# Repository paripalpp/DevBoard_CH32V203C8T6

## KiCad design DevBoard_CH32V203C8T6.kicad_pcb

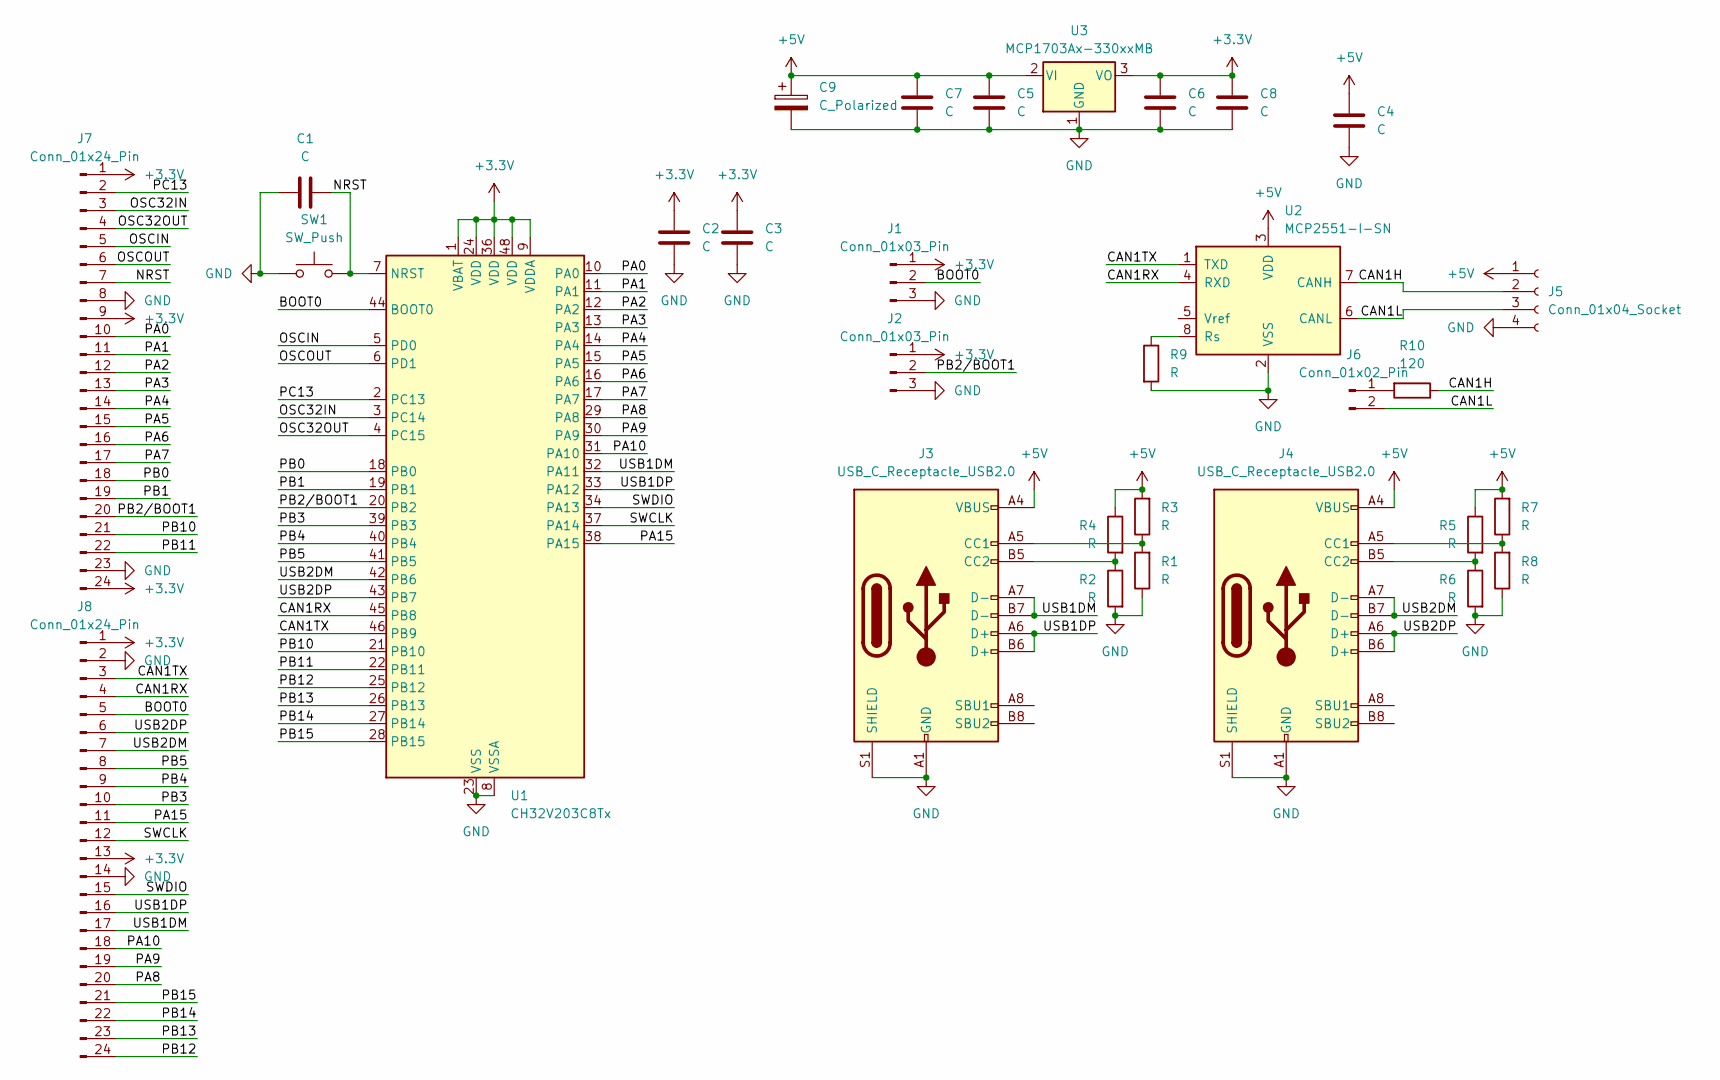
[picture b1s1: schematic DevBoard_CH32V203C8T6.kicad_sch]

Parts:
C1, C2, C3, C4, C5, C6: C; C_0603_1608Metric
C7, C8: C; C_0805_2012Metric
C9: C_Polarized; CP_Elec_6.3x7.7
J1, J2: Conn_01x03_Pin; PinHeader_1x03_P2.54mm_Vertical
J3, J4: USB_C_Receptacle_USB2.0; USB_C_Receptacle_G-Switch_GT-USB-7010ASV
J5: Conn_01x04_Socket; JST_XA_S04B-XASK-1_1x04_P2.50mm_Horizontal
J6: Conn_01x02_Pin; PinHeader_1x02_P2.54mm_Vertical
J7, J8: Conn_01x24_Pin; PinHeader_2x12_P2.54mm_Vertical
R1, R2, R3, R4, R5, R6, R7, R8, R9: R; R_0603_1608Metric
R10: 120; R_0603_1608Metric
SW1: SW_Push; TVAF06-A020B-R
U1: CH32V203C8Tx; LQFP-48_7x7mm_P0.5mm
U2: MCP2551-I-SN; SOIC-8_3.9x4.9mm_P1.27mm
U3: MCP1703Ax-330xxMB; SOT-89-3

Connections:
+3.3V: C2.1, C3.1, C6.1, C8.1, J1.1, J2.1, J7.1, J7.9, J7.24, J8.1, J8.13, U1.1 (VBAT), U1.9 (VDDA), U1.24 (VDD), U1.36 (VDD), U1.48 (VDD), U3.3 (VO)
+5V: C4.1, C5.1, C7.1, C9.1, J3.A4 (VBUS), J3.A9 (VBUS), J3.B4 (VBUS), J3.B9 (VBUS), J4.A4 (VBUS), J4.A9 (VBUS), J4.B4 (VBUS), J4.B9 (VBUS), J5.1, R3.2, R4.1, R5.1, R7.2, U2.3 (VDD), U3.2 (VI)
/BOOT0: J1.2, J8.5, U1.44 (BOOT0)
/CAN1H: J5.2, R10.1, U2.7 (CANH)
/CAN1L: J5.3, J6.2, U2.6 (CANL)
/CAN1RX: J8.4, U1.45 (PB8), U2.4 (RXD)
/CAN1TX: J8.3, U1.46 (PB9), U2.1 (TXD)
/NRST: C1.2, J7.7, SW1.2, U1.7 (NRST)
/OSC32IN: J7.3, U1.3 (PC14)
/OSC32OUT: J7.4, U1.4 (PC15)
/OSCIN: J7.5, U1.5 (PD0)
/OSCOUT: J7.6, U1.6 (PD1)
/PA0: J7.10, U1.10 (PA0)
/PA1: J7.11, U1.11 (PA1)
/PA2: J7.12, U1.12 (PA2)
/PA3: J7.13, U1.13 (PA3)
/PA4: J7.14, U1.14 (PA4)
/PA5: J7.15, U1.15 (PA5)
/PA6: J7.16, U1.16 (PA6)
/PA7: J7.17, U1.17 (PA7)
/PA8: J8.20, U1.29 (PA8)
/PA9: J8.19, U1.30 (PA9)
/PA10: J8.18, U1.31 (PA10)
/PA15: J8.11, U1.38 (PA15)
/PB0: J7.18, U1.18 (PB0)
/PB1: J7.19, U1.19 (PB1)
/PB2/BOOT1: J2.2, J7.20, U1.20 (PB2)
/PB3: J8.10, U1.39 (PB3)
/PB4: J8.9, U1.40 (PB4)
/PB5: J8.8, U1.41 (PB5)
/PB10: J7.21, U1.21 (PB10)
/PB11: J7.22, U1.22 (PB11)
/PB12: J8.24, U1.25 (PB12)
/PB13: J8.23, U1.26 (PB13)
/PB14: J8.22, U1.27 (PB14)
/PB15: J8.21, U1.28 (PB15)
/PC13: J7.2, U1.2 (PC13)
/SWCLK: J8.12, U1.37 (PA14)
/SWDIO: J8.15, U1.34 (PA13)
/USB1DM: J3.A7 (D-), J3.B7 (D-), J8.17, U1.32 (PA11)
/USB1DP: J3.A6 (D+), J3.B6 (D+), J8.16, U1.33 (PA12)
/USB2DM: J4.A7 (D-), J4.B7 (D-), J8.7, U1.42 (PB6)
/USB2DP: J4.A6 (D+), J4.B6 (D+), J8.6, U1.43 (PB7)
GND: C1.1, C2.2, C3.2, C4.2, C5.2, C6.2, C7.2, C8.2, C9.2, J1.3, J2.3, J3.A1 (GND), J3.A12 (GND), J3.B1 (GND), J3.B12 (GND), J3.S1 (SHIELD), J4.A1 (GND), J4.A12 (GND), J4.B1 (GND), J4.B12 (GND), J4.S1 (SHIELD), J5.4, J7.8, J7.23, J8.2, J8.14, R1.1, R2.2, R6.2, R8.1, R9.2, SW1.1, U1.8 (VSSA), U1.23 (VSS), U1.35 (VSS), U1.47 (VSS), U1.49 (VSS), U2.2 (VSS), U3.1 (GND)
unnamed: J3.A5 (CC1), R1.2, R3.1
unnamed: J3.B5 (CC2), R2.1, R4.2
unnamed: J4.A5 (CC1), R7.1, R8.2
unnamed: J4.B5 (CC2), R5.2, R6.1
unnamed: J6.1, R10.2
unnamed: R9.1, U2.8 (Rs)

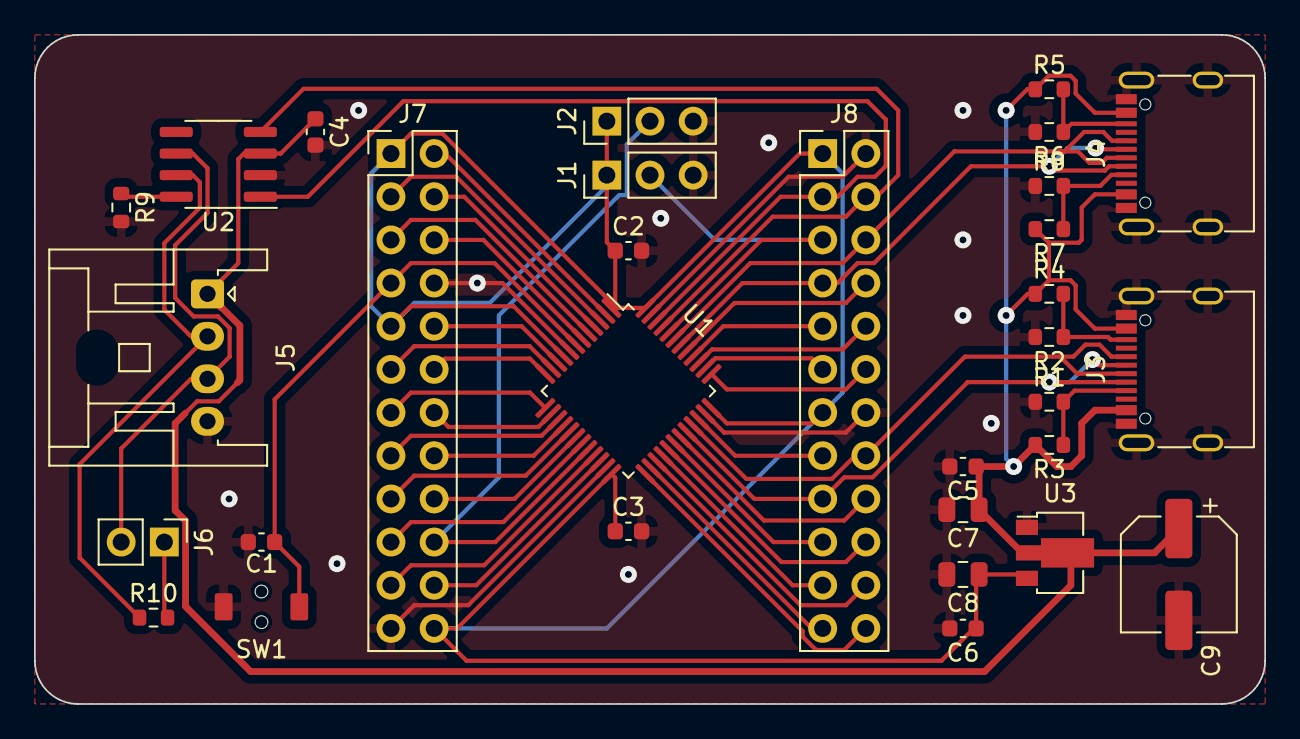
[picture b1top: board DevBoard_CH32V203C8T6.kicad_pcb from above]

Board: 2 copper layers, 72.4 x 39.4 mm, 31 parts (0 on the bottom side), 50 nets.
